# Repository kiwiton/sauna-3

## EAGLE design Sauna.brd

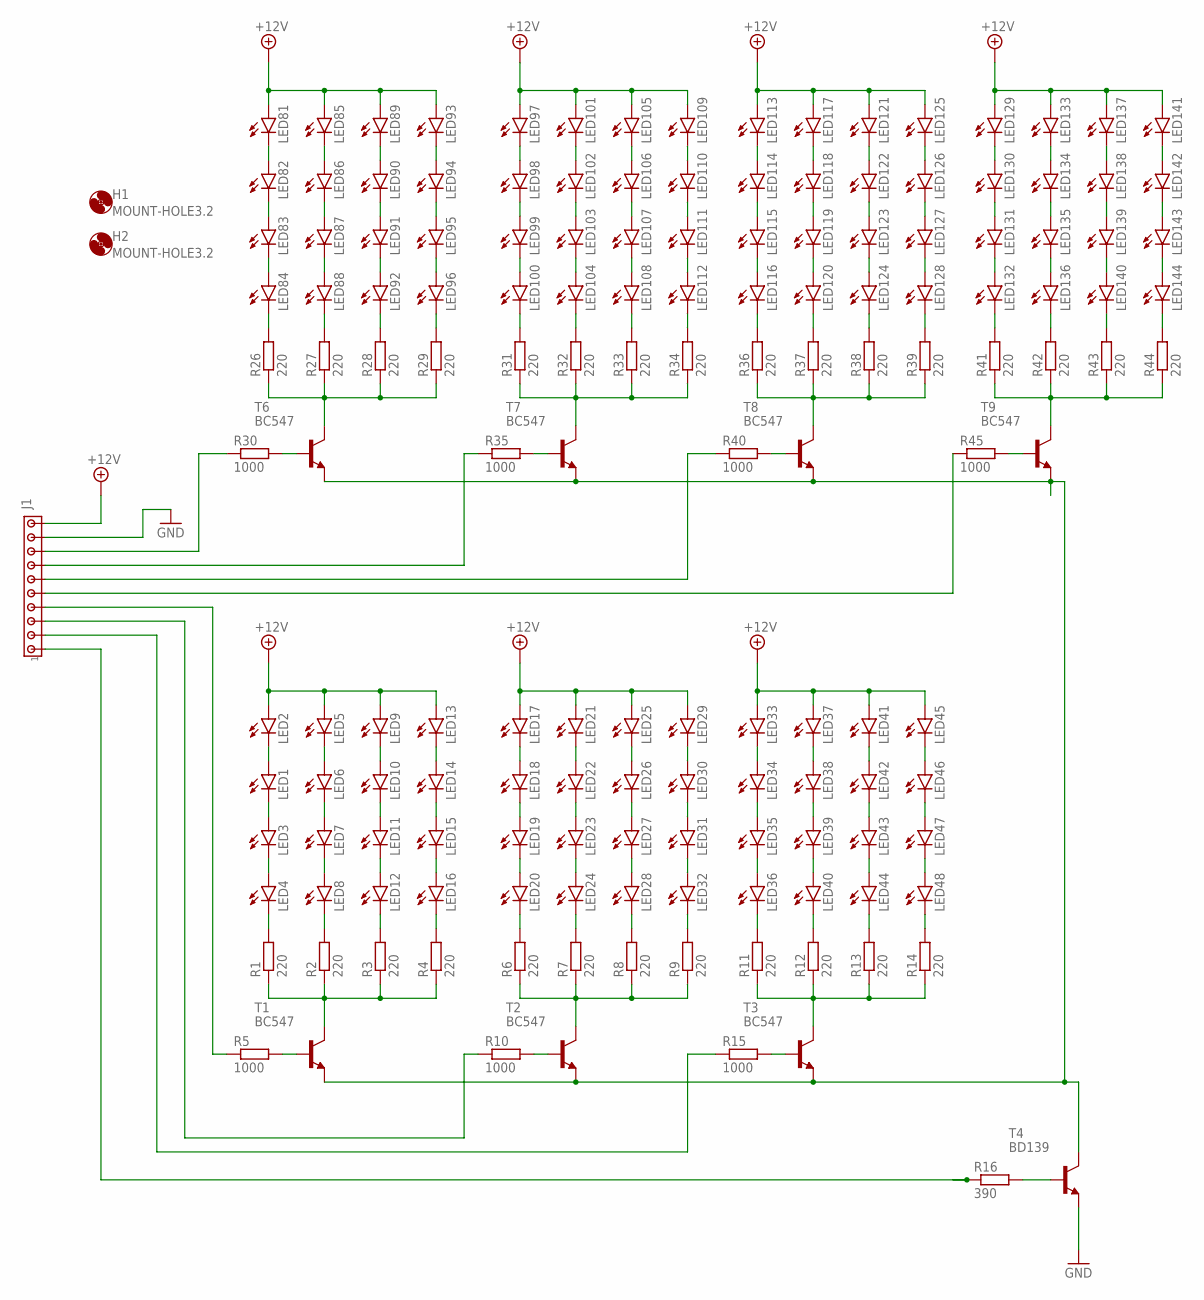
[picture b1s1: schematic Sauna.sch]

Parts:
H1, H2: MOUNT-HOLE3.2; 3,2
J1: MTA10-100; 10X10MTA
LED1, LED2, LED3, LED4, LED5, LED6, LED7, LED8, LED9, LED10, LED11, LED12, LED13, LED14, LED15, LED16, LED17, LED18, LED19, LED20, LED21, LED22, LED23, LED24, LED25, LED26, LED27, LED28, LED29, LED30, LED31, LED32, LED33, LED34, LED35, LED36, LED37, LED38, LED39, LED40, LED41, LED42, LED43, LED44, LED45, LED46, LED47, LED48, LED81, LED82, LED83, LED84, LED85, LED86, LED87, LED88, LED89, LED90, LED91, LED92, LED93, LED94, LED95, LED96, LED97, LED98, LED99, LED100, LED101, LED102, LED103, LED104, LED105, LED106, LED107, LED108, LED109, LED110, LED111, LED112, LED113, LED114, LED115, LED116, LED117, LED118, LED119, LED120, LED121, LED122, LED123, LED124, LED125, LED126, LED127, LED128, LED129, LED130, LED131, LED132, LED133, LED134, LED135, LED136, LED137, LED138, LED139, LED140, LED141, LED142, LED143, LED144: LED5MM
R1, R2, R3, R4, R6, R7, R8, R9, R11, R12, R13, R14, R26, R27, R28, R29, R31, R32, R33, R34, R36, R37, R38, R39, R41, R42, R43, R44: 220; 0207/10
R5, R10, R15, R30, R35, R40, R45: 1000; 0207/10
R16: 390; 0207/10
T1, T2, T3, T6, T7, T8, T9: BC547; TO92
T4: BD139; TO126

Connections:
+12V: J1.10, LED2.A, LED5.A, LED9.A, LED13.A, LED17.A, LED21.A, LED25.A, LED29.A, LED33.A, LED37.A, LED41.A, LED45.A, LED81.A, LED85.A, LED89.A, LED93.A, LED97.A, LED101.A, LED105.A, LED109.A, LED113.A, LED117.A, LED121.A, LED125.A, LED129.A, LED133.A, LED137.A, LED141.A
GND: J1.9, T4.1 (E)
unnamed: LED1.A, LED2.K (C)
unnamed: LED1.K (C), LED3.A
unnamed: LED3.K (C), LED4.A
unnamed: LED5.K (C), LED6.A
unnamed: LED6.K (C), LED7.A
unnamed: LED7.K (C), LED8.A
unnamed: LED9.K (C), LED10.A
unnamed: LED10.K (C), LED11.A
unnamed: LED11.K (C), LED12.A
unnamed: LED13.K (C), LED14.A
unnamed: LED14.K (C), LED15.A
unnamed: LED15.K (C), LED16.A
unnamed: R16.2, T4.3 (B)
unnamed: LED16.K (C), R4.2
unnamed: LED4.K (C), R1.2
unnamed: LED8.K (C), R2.2
unnamed: LED12.K (C), R3.2
unnamed: R1.1, R2.1, R3.1, R4.1, T1.3 (C)
unnamed: R5.2, T1.2 (B)
unnamed: LED17.K (C), LED18.A
unnamed: LED18.K (C), LED19.A
unnamed: LED19.K (C), LED20.A
unnamed: LED21.K (C), LED22.A
unnamed: LED22.K (C), LED23.A
unnamed: LED23.K (C), LED24.A
unnamed: LED25.K (C), LED26.A
unnamed: LED26.K (C), LED27.A
unnamed: LED27.K (C), LED28.A
unnamed: LED29.K (C), LED30.A
unnamed: LED30.K (C), LED31.A
unnamed: LED31.K (C), LED32.A
unnamed: LED32.K (C), R9.2
unnamed: LED20.K (C), R6.2
unnamed: LED24.K (C), R7.2
unnamed: LED28.K (C), R8.2
unnamed: R6.1, R7.1, R8.1, R9.1, T2.3 (C)
unnamed: R10.2, T2.2 (B)
unnamed: LED33.K (C), LED34.A
unnamed: LED34.K (C), LED35.A
unnamed: LED35.K (C), LED36.A
unnamed: LED37.K (C), LED38.A
unnamed: LED38.K (C), LED39.A
unnamed: LED39.K (C), LED40.A
unnamed: LED41.K (C), LED42.A
unnamed: LED42.K (C), LED43.A
unnamed: LED43.K (C), LED44.A
unnamed: LED45.K (C), LED46.A
unnamed: LED46.K (C), LED47.A
unnamed: LED47.K (C), LED48.A
unnamed: LED48.K (C), R14.2
unnamed: LED36.K (C), R11.2
unnamed: LED40.K (C), R12.2
unnamed: LED44.K (C), R13.2
unnamed: R11.1, R12.1, R13.1, R14.1, T3.3 (C)
unnamed: R15.2, T3.2 (B)
unnamed: J1.2, R15.1
unnamed: J1.8, R30.1
unnamed: J1.1, R16.1
unnamed: T1.1 (E), T2.1 (E), T3.1 (E), T4.2 (C), T6.1 (E), T7.1 (E), T8.1 (E), T9.1 (E)
unnamed: LED81.K (C), LED82.A
unnamed: LED82.K (C), LED83.A
unnamed: LED83.K (C), LED84.A
unnamed: LED85.K (C), LED86.A
unnamed: LED86.K (C), LED87.A
unnamed: LED87.K (C), LED88.A
unnamed: LED89.K (C), LED90.A
unnamed: LED90.K (C), LED91.A
unnamed: LED91.K (C), LED92.A
unnamed: LED93.K (C), LED94.A
unnamed: LED94.K (C), LED95.A
unnamed: LED95.K (C), LED96.A
unnamed: LED96.K (C), R29.2
unnamed: LED84.K (C), R26.2
unnamed: LED88.K (C), R27.2
unnamed: LED92.K (C), R28.2
unnamed: R26.1, R27.1, R28.1, R29.1, T6.3 (C)
unnamed: R30.2, T6.2 (B)
unnamed: LED97.K (C), LED98.A
unnamed: LED98.K (C), LED99.A
unnamed: LED99.K (C), LED100.A
unnamed: LED101.K (C), LED102.A
unnamed: LED102.K (C), LED103.A
unnamed: LED103.K (C), LED104.A
unnamed: LED105.K (C), LED106.A
unnamed: LED106.K (C), LED107.A
unnamed: LED107.K (C), LED108.A
unnamed: LED109.K (C), LED110.A
unnamed: LED110.K (C), LED111.A
unnamed: LED111.K (C), LED112.A
unnamed: LED112.K (C), R34.2
unnamed: LED100.K (C), R31.2
unnamed: LED104.K (C), R32.2
unnamed: LED108.K (C), R33.2
unnamed: R31.1, R32.1, R33.1, R34.1, T7.3 (C)
unnamed: R35.2, T7.2 (B)
unnamed: LED113.K (C), LED114.A
unnamed: LED114.K (C), LED115.A
unnamed: LED115.K (C), LED116.A
unnamed: LED117.K (C), LED118.A
unnamed: LED118.K (C), LED119.A
unnamed: LED119.K (C), LED120.A
unnamed: LED121.K (C), LED122.A
unnamed: LED122.K (C), LED123.A
unnamed: LED123.K (C), LED124.A
unnamed: LED125.K (C), LED126.A
unnamed: LED126.K (C), LED127.A
unnamed: LED127.K (C), LED128.A
unnamed: LED128.K (C), R39.2
unnamed: LED116.K (C), R36.2
unnamed: LED120.K (C), R37.2
unnamed: LED124.K (C), R38.2
unnamed: R36.1, R37.1, R38.1, R39.1, T8.3 (C)
unnamed: R40.2, T8.2 (B)
unnamed: LED129.K (C), LED130.A
unnamed: LED130.K (C), LED131.A
unnamed: LED131.K (C), LED132.A
unnamed: LED133.K (C), LED134.A
unnamed: LED134.K (C), LED135.A
unnamed: LED135.K (C), LED136.A
unnamed: LED137.K (C), LED138.A
unnamed: LED138.K (C), LED139.A
unnamed: LED139.K (C), LED140.A
unnamed: LED141.K (C), LED142.A
unnamed: LED142.K (C), LED143.A
unnamed: LED143.K (C), LED144.A
unnamed: LED144.K (C), R44.2
unnamed: LED132.K (C), R41.2
unnamed: LED136.K (C), R42.2
unnamed: LED140.K (C), R43.2
unnamed: R41.1, R42.1, R43.1, R44.1, T9.3 (C)
unnamed: R45.2, T9.2 (B)
unnamed: J1.7, R35.1
unnamed: J1.6, R40.1
unnamed: J1.5, R45.1
unnamed: J1.4, R5.1
unnamed: J1.3, R10.1

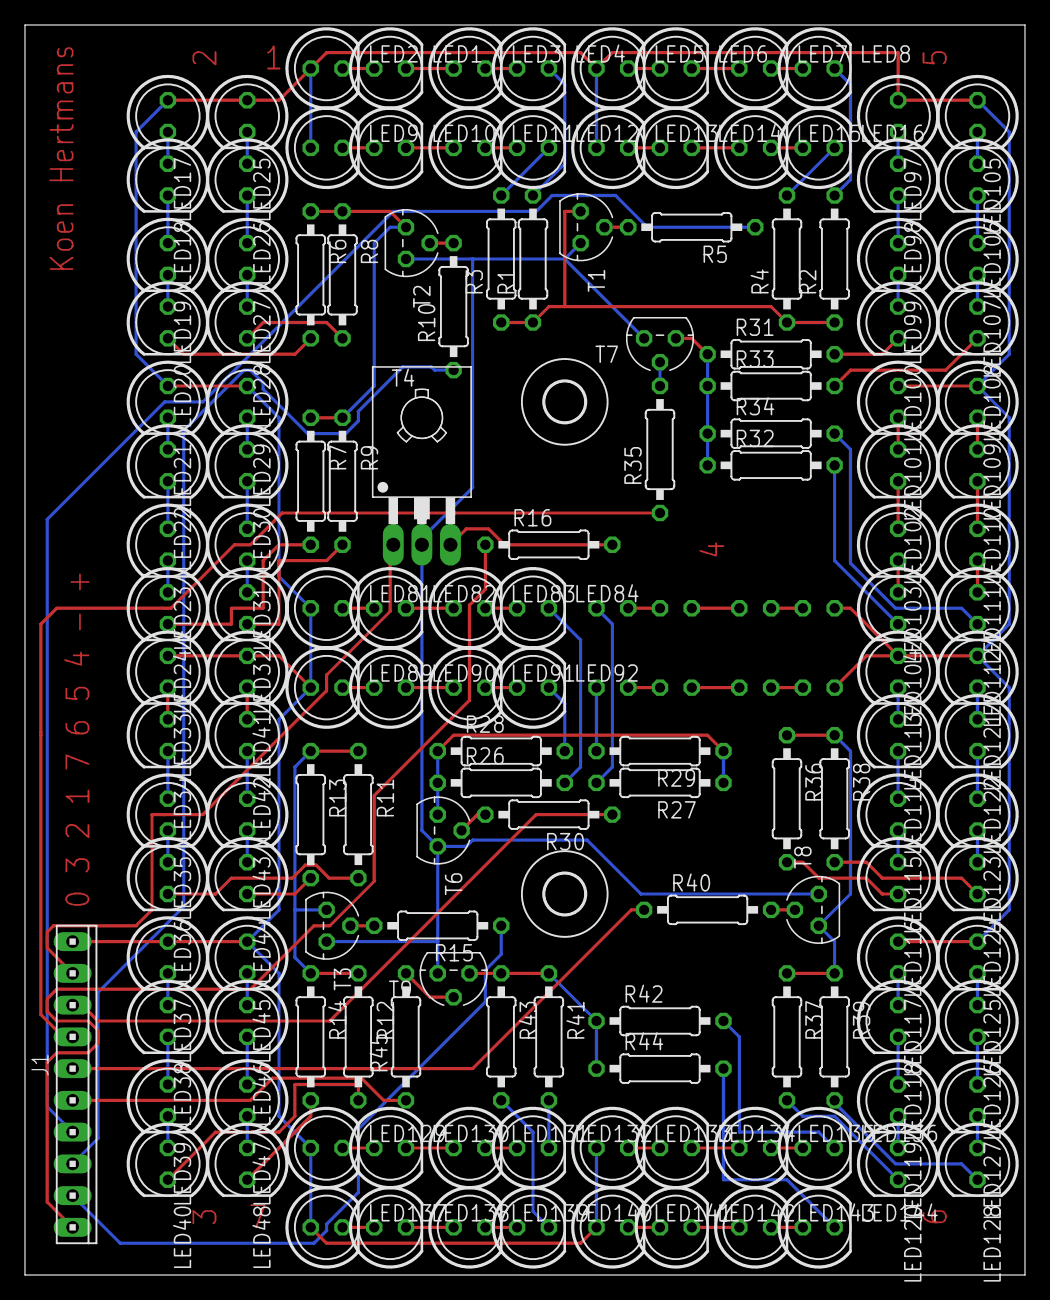
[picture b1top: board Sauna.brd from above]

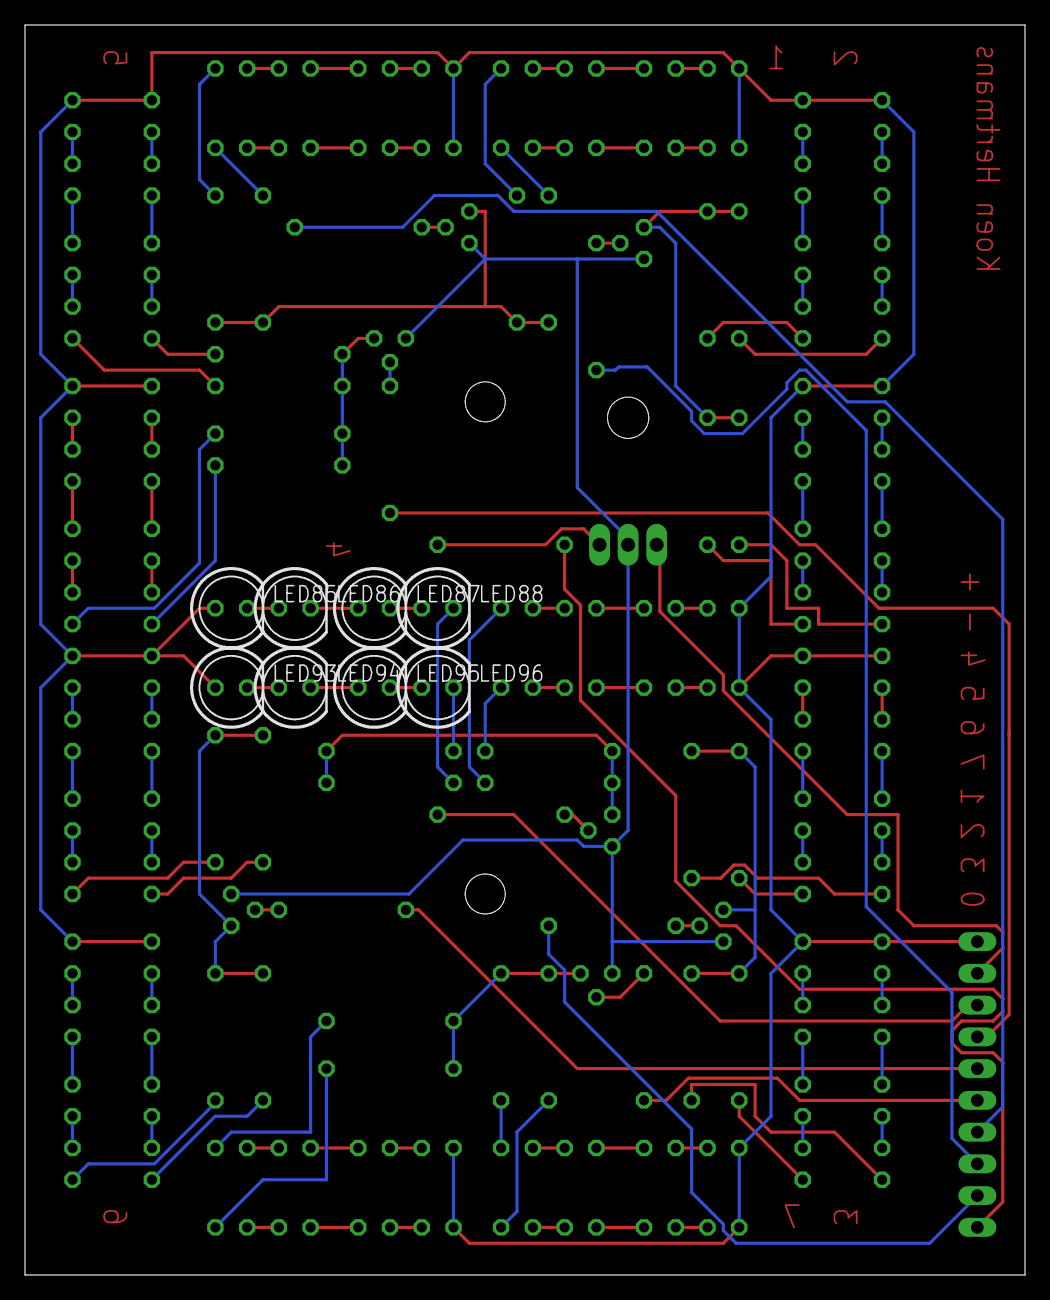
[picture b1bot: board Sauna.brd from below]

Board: 2 copper layers, 80.0 x 100.0 mm, 159 parts (8 on the bottom side), 138 nets.

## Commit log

2020-02-13 Add files via upload
    in dit bestand staat opgelijst wat de I/O is van ons project
